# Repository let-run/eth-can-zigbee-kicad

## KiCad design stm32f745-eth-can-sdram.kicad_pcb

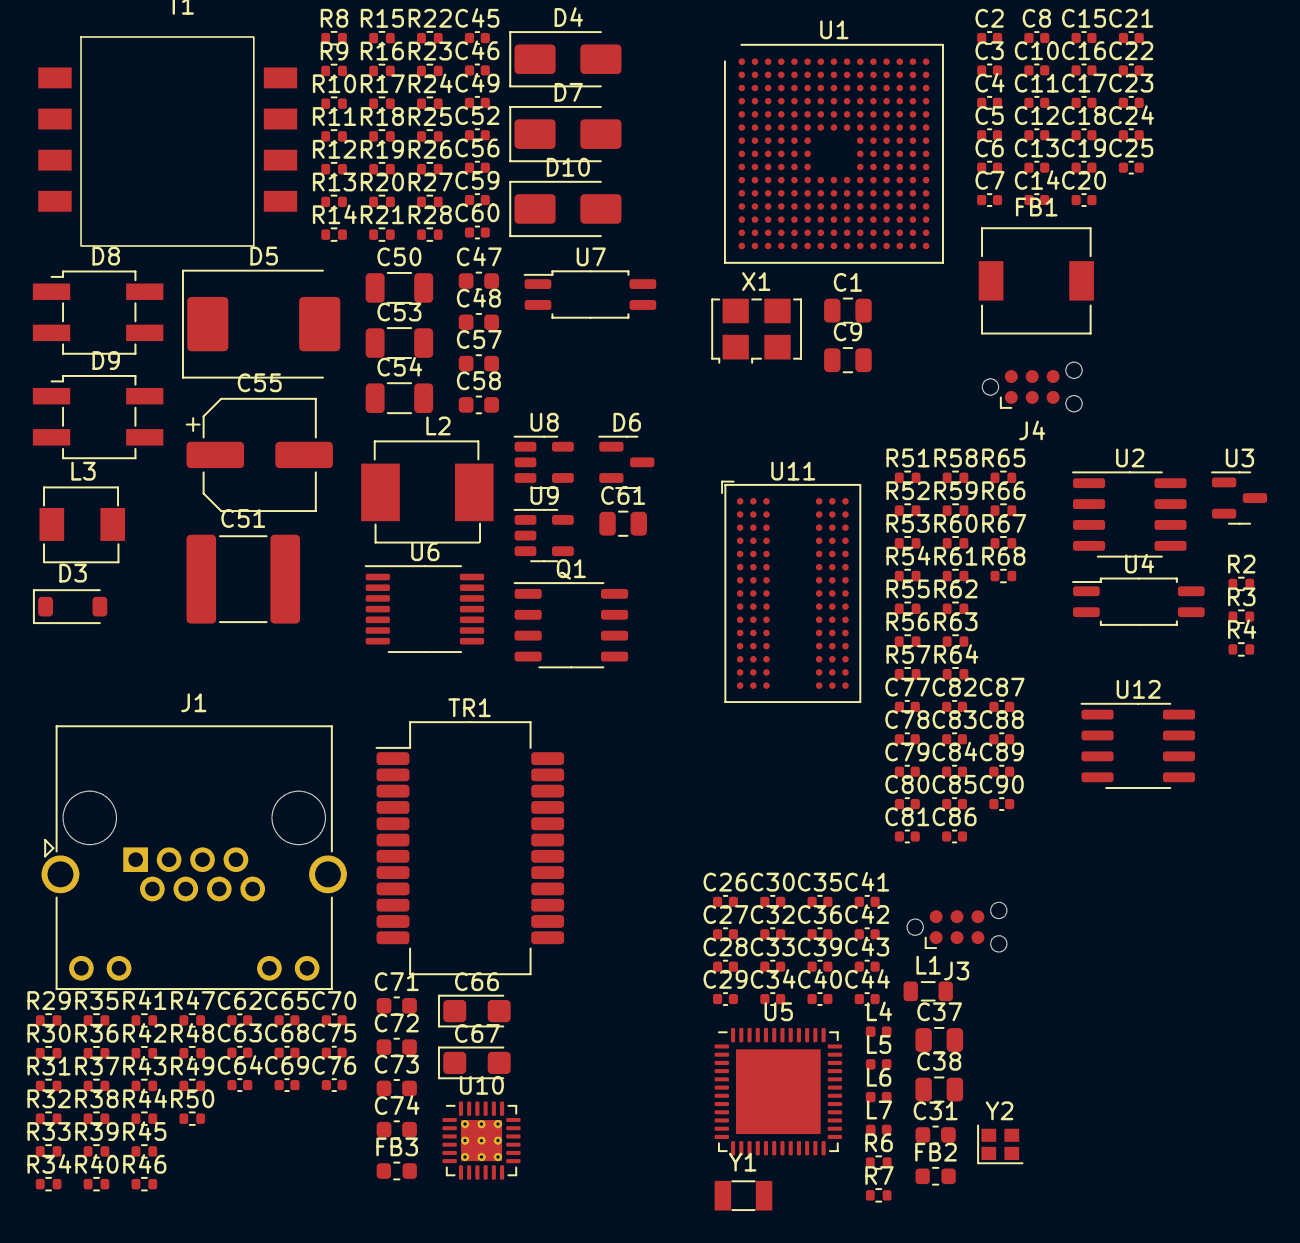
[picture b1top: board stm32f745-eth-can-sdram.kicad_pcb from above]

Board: 2 copper layers, 195 parts (0 on the bottom side), 148 nets, no tracks yet.

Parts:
C1: 100n; C_0805_2012Metric
C2: 10u; C_0402_1005Metric
C3, C5, C7, C8, C10, C11, C12, C13, C14, C15, C16, C17, C18, C19, C20, C21, C22, C23, C24, C25, C32, C33, C34, C35, C36, C39, C40, C46, C62, C63, C64, C65, C68, C76, C77, C78, C79, C80, C81, C82, C83, C84, C85, C86, C87, C88, C89, C90: 100n; C_0402_1005Metric
C4: 10n; C_0402_1005Metric
C6: 1u; C_0402_1005Metric
C9: 1u; C_0805_2012Metric
C26, C27, C28, C41, C42, C43, C44: 1pF; C_0402_1005Metric
C29, C30: 12pF; C_0402_1005Metric
C31, C48: 10uF; C_0603_1608Metric
C37, C38: 22uF; C_0805_2012Metric
C45, C75: DNP; C_0402_1005Metric
C47: 1uF; C_0603_1608Metric
C49, C60: 0.1uF; C_0402_1005Metric
C50: 2.2uF; C_1206_3216Metric
C51: 10uF; C_2220_5650Metric
C52: 1000pF; C_0402_1005Metric
C53, C54: 22uF; C_1206_3216Metric
C55: 470uF; CP_Elec_6.3x7.7
C56, C69: 1uF; C_0402_1005Metric
C57: 0.015uF; C_0603_1608Metric
C58: 470pF; C_0603_1608Metric
C59: 0.022uF; C_0402_1005Metric
C61: 1000pF; C_0805_2012Metric
C66, C67: 10uF; CP_EIA-3216-18_Kemet-A
C70: 470pF; C_0402_1005Metric
C71, C72, C73, C74: 22nF; C_0603_1608Metric
D3: MMSD4148; D_SOD-123
D4, D10: MURA120; D_SMA
D5: MBRS540; D_SMC
D6: BAT54S; SOT-23
D7: SMAJ58A; D_SMA
D8, D9: HD01
FB1: 120R; L_6.3x6.3_H3
FB2: BLM18HE152SN1D; L_0603_1608Metric
FB3: BLM18PG121; L_0603_1608Metric
J1: 8P8C_LED_Shielded; RJ45_Amphenol_RJHSE538X
J3: JTAG; Tag-Connect_TC2030-IDC-NL_2x03_P1.27mm_Vertical
J4: SWO; Tag-Connect_TC2030-IDC-NL_2x03_P1.27mm_Vertical
L1: 6.8uH; L_0805_2012Metric
L2: 3.3uH; L_6.6x7.2_H3
L3: 0.33uH; L_4.4x4.2_H2
L4: LQG15HS1(2nH); L_0402_1005Metric
L5: LQG15HS2(2nH); L_0402_1005Metric
L6, L7: LQG15HS2(2.4nH); L_0402_1005Metric
Q1: Si4848DY; SOP-8_3.9x4.9mm_P1.27mm
R2: 40k; R_0402_1005Metric
R3: 5k; R_0402_1005Metric
R4: 575; R_0402_1005Metric
R6, R7: 1k; R_0402_1005Metric
R8: 24.9k; R_0402_1005Metric
R9: 1.27k; R_0402_1005Metric
R10: 39.2k; R_0402_1005Metric
R11: 80.6k; R_0402_1005Metric
R12: 59k; R_0402_1005Metric
R13: 392k; R_0402_1005Metric
R14, R17, R18, R20: 10R; R_0402_1005Metric
R15, R22: 1K; R_0402_1005Metric
R16: 0.5(0.25W); R_0402_1005Metric
R19: 39K; R_0402_1005Metric
R21: 575R; R_0402_1005Metric
R23: 2K; R_0402_1005Metric
R24: 11K; R_0402_1005Metric
R25: 34K; R_0402_1005Metric
R26: 1.5K; R_0402_1005Metric
R27: 301R; R_0402_1005Metric
R28: 0; R_0402_1005Metric
R29, R30, R31: 33; R_0402_1005Metric
R32: 100; R_0402_1005Metric
R33, R34, R35, R36, R37: 4.7K; R_0402_1005Metric
R38, R39, R40, R41: 50; R_0402_1005Metric
R42: 12.1K; R_0402_1005Metric
R43, R44: 330; R_0402_1005Metric
R45, R46, R51, R52, R53, R54, R55, R56, R57, R58, R59, R60, R61, R62, R63, R64, R65, R66, R67, R68: 10K; R_0402_1005Metric
R47, R48, R49, R50: 75; R_0402_1005Metric
T1: POE70P-50L; POE70P
TR1: 30F-51NL; Transformer_Ethernet_YDS_30F-51NL_SO-24_7.1x15.1mm
U1: STM32F746NGHx; TFBGA-216_13x13mm_Layout15x15_P0.8mm
U2, U12: TJA1051T; SOIC-8_3.9x4.9mm_P1.27mm
U3: TL431(2.5-36); SOT-23
U4, U7: TCMT1107; SOP-4_4.4x2.6mm_P1.27mm
U5: VQFN-48-1EP_7x7mm_P0.5mm_EP5.15x5.15mm
U6: TPS23753; TSSOP-14_4.4x5mm_P0.65mm
U8: TLV431AIDBVR; SOT-23-5
U9: TPS73633DBV; SOT-23-5
U10: LAN8742A; VQFN-24-1EP_4x4mm_P0.5mm_EP2.5x2.5mm_ThermalVias
U11: IS42S32800J-7BLI; BGA-90_8.0x13.0mm_Layout2x3x15_P0.8mm
X1: SG-5032CAN; Oscillator_SMD_SeikoEpson_SG8002LB-4Pin_5.0x3.2mm
Y1: 32.768kHz; Crystal_SMD_3215-2Pin_3.2x1.5mm
Y2: Q22FA12800150; Crystal_SMD_2016-4Pin_2.0x1.6mm

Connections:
+3.3V: C2.1, C3.1, C5.1, C7.1, C8.1, C9.1, C10.1, C11.1, C12.1, C13.1, C14.1, C15.1, C16.1, C17.1, C18.1, C19.1, C20.1, C21.1, C22.1, C23.1, C24.1, C25.1, C62.1, C63.1, C67.1, C68.1, C76.1, C77.1, C78.1, C79.1, C80.1, C81.1, C82.1, C83.1, C84.1, C85.1, C86.1, C87.1, C88.1, C89.1, C90.1, FB1.1, FB2.2, FB3.2, J4.5 (GND), R33.2, R34.2, R35.2, R36.2, R37.2, R38.2, R39.2, R40.2, R41.2, TR1.7 (CT), TR1.10 (CT), U1.C1 (VBAT), U1.E7 (VDD), U1.E8 (VDD), U1.E9 (VDD), U1.E10 (VDD), U1.F4 (VDD), U1.F5 (VDD), U1.F11 (VDD), U1.G5 (VDD), U1.H5 (VDD), U1.H11 (VDD), U1.J5 (VDD), U1.J11 (VDD), U1.K5 (VDD), U1.K11 (VDD), U1.L7 (VDD), U1.L8 (VDD), U1.L9 (VDD), U1.L10 (VDD), U10.9 (VDDIO), U11.A7 (VDD), U11.B2 (VDDQ), U11.B7 (VDDQ), U11.C9 (VDDQ), U11.D9 (VDDQ), U11.E1 (VDDQ), U11.F9 (VDD), U11.L1 (VDDQ), U11.L7 (VDD), U11.M9 (VDDQ), U11.N9 (VDDQ), U11.P2 (VDDQ), U11.P7 (VDDQ), U11.R7 (VDD)
+3.3VA: C4.1, C6.1, FB1.2
+5V: C55.1, L3.2, R28.2, U2.3 (VCC), U12.3 (VCC)
+24V: R2.2, R4.2
/Zigbee/DCDC_SW: L1.1, U5.33 (DCDC_SW)
/Zigbee/VDDR: C38.1, C39.1, C40.1, L1.2, U5.45 (VDDR), U5.48 (VDDR_RF)
/Zigbee/VDDS: C33.1, C34.1, C35.1, C36.1, C37.1, FB2.1, U5.13 (VDDS2), U5.22 (VDDS3), U5.34 (VDDS_DCDC), U5.44 (VDDS)
AUX: D10.2 (A), R13.2
ETH_LED1: J1.12, R46.2, U10.3 (LED1/REGOFF)
ETH_LED2: J1.10, R45.1, U10.2 (LED2/~INTSEL)
FMC_A0: U1.D2 (PF0), U11.G8 (A0)
FMC_A1: U1.E2 (PF1), U11.G9 (A1)
FMC_A2: U1.G2 (PF2), U11.F7 (A2)
FMC_A3: U1.H2 (PF3), U11.F3 (A3)
FMC_A4: U1.J2 (PF4), U11.G1 (A4)
FMC_A5: U1.K3 (PF5), U11.G2 (A5)
FMC_A6: U1.M6 (PF12), U11.G3 (A6)
FMC_A7: U1.N6 (PF13), U11.H1 (A7)
FMC_A8: U1.M8 (PF15), U1.P6 (PF14), U11.H2 (A8)
FMC_A10: U1.N7 (PG0), U11.G7 (A10)
FMC_A11: U1.M7 (PG1), U11.H9 (A11)
FMC_BA0: U1.N12 (PG4), U11.J7 (BA0)
FMC_BA1: U1.N11 (PG5), U11.H8 (BA1)
FMC_D0: U1.L12 (PD14), U11.R8 (DQ0)
FMC_D1: U1.K13 (PD15), U11.N7 (DQ1)
FMC_D2: U1.B12 (PD0), U11.R9 (DQ2)
FMC_D3: U1.C12 (PD1), U11.N8 (DQ3)
FMC_D4: U1.R8 (PE7), U11.P9 (DQ4)
FMC_D5: U1.N9 (PE8), U11.M8 (DQ5)
FMC_D6: U1.P9 (PE9), U11.M7 (DQ6)
FMC_D7: U1.R9 (PE10), U11.L8 (DQ7)
FMC_D8: U1.P10 (PE11), U11.L2 (DQ8)
FMC_D9: U1.R10 (PE12), U11.M3 (DQ9)
FMC_D10: U1.R12 (PE13), U11.M2 (DQ10)
FMC_D11: U1.P11 (PE14), U11.P1 (DQ11)
FMC_D12: U1.R11 (PE15), U11.N2 (DQ12)
FMC_D13: U1.L15 (PD8), U11.R1 (DQ13)
FMC_D14: U1.L14 (PD9), U11.N3 (DQ14)
FMC_D15: U1.K15 (PD10), U11.R2 (DQ15)
FMC_NBL0: U1.A6 (PE0), U11.K9 (DQM0)
FMC_NBL1: U1.A5 (PE1), U11.K1 (DQM1)
FMC_SDCKE0: U1.K4 (PH2), U11.J2 (CKE)
FMC_SDCLK: U1.H14 (PG8), U11.J1 (CLK)
FMC_SDNCAS: U1.B7 (PG15), U11.K7 (~CAS)
FMC_SDNE0: U1.J4 (PH3), U11.J8 (~CS)
FMC_SDNRAS: U1.P8 (PF11), U11.J9 (~RAS)
FMC_SDNWE: U1.J3 (PH5), U11.K8 (~WE)
GND: C1.2, C2.2, C3.2, C4.2, C5.2, C6.2, C7.2, C8.2, C9.2, C10.2, C11.2, C12.2, C13.2, C14.2, C15.2, C16.2, C17.2, C18.2, C19.2, C20.2, C21.2, C22.2, C23.2, C24.2, C25.2, C26.2, C27.2, C29.1, C31.2, C32.2, C33.2, C34.2, C35.2, C36.2, C37.2, C38.2, C39.2, C40.2, C41.2, C42.2, C43.2, C44.2, C53.2, C54.2, C55.2, C56.2, C62.2, C63.2, C64.2, C65.2, C66.2, C67.2, C68.2, C69.1, C70.1, C75.2, C76.2, C77.2, C78.2, C79.2, C80.2, C81.2, C82.2, C83.2, C84.2, C85.2, C86.2, C87.2, C88.2, C89.2, C90.2, J3.5 (GND), J4.1 (VCC), R6.2, R7.2, R24.1, R42.1, R43.2, R44.1, R45.2, R46.1, R51.2, R52.2, R53.2, R54.2, R55.2, R56.2, R57.2, R58.2, R59.2, R60.2, R61.2, R62.2, R63.2, R64.2, R65.2, R66.2, R67.2, R68.2, T1.5, T1.6, U2.2 (GND), U2.8 (S), U5.49 (EP), U8.5 (A), U10.25 (VSS), U11.A3 (VSS), U11.B3 (VSSQ), U11.B8 (VSSQ), U11.C1 (VSSQ), U11.D1 (VSSQ), U11.E9 (VSSQ), U11.F1 (VSS), U11.L3 (VSS), U11.L9 (VSSQ), U11.M1 (VSSQ), U11.N1 (VSSQ), U11.P3 (VSSQ), U11.P8 (VSSQ), U11.R3 (VSS), U12.2 (GND), U12.8 (S), Y2.2, Y2.4
GND1: C45.2, C46.2, C47.2, C48.2, C50.2, C51.2, J1.SH, R3.1, R10.1, R11.1, R12.1, R16.1, T1.2, U3.3 (A), U6.6 (RTN), U7.3
JTAG_TCK: J3.4 (SWCLK), U5.25 (JTAG_TCKC)
JTAG_TDI: J3.2 (SWDIO), U5.27 (DIO_17)
JTAG_TDO: J3.6 (SWO), U5.26 (DIO_16)
JTAG_TMS: J3.1 (VCC), U5.24 (JTAG_TMSC)
NRST: C1.1, J4.3 (~RESET), U1.J1 (NRST), U10.15 (~RST)
unnamed: C26.1, L4.1, L5.2
unnamed: C28.1, L5.1, L6.2
unnamed: C29.2, L7.2
unnamed: C30.2, L4.2
unnamed: C49.1, C50.1, L2.2, R19.2, T1.3
unnamed: C52.1, R20.2
unnamed: C57.1, R23.1
unnamed: C59.1, R27.2
unnamed: C71.1, R49.1
unnamed: C72.1, R47.1
unnamed: C73.1, R50.1
unnamed: C74.1, R48.1
unnamed: C75.1, R47.2, R48.2, R49.2, R50.2
unnamed: D3.2 (A), R17.1
unnamed: C47.1, C48.1, D3.1 (K)
unnamed: D4.2 (A), Q1.5 (D), Q1.6 (D), Q1.7 (D), Q1.8 (D), T1.4
unnamed: C49.2, D4.1 (K), R19.1
unnamed: D5.2 (A), R20.1, T1.7, T1.8
unnamed: C52.2, C53.1, C54.1, D5.1 (K), L3.1
unnamed: C58.1, D6.1 (A), R23.2, U7.2, U8.3 (K)
unnamed: C56.1, D6.3 (COM), R22.1
unnamed: D6.2 (K), R21.2, R22.2, R25.2, R28.1
unnamed: J1.9, R43.1
unnamed: J1.11, R44.2
unnamed: Q1.4 (G), R14.2
unnamed: Q1.1 (S), Q1.2 (S), Q1.3 (S), R15.2, R16.2
unnamed: R4.1, U4.1
unnamed: R17.2, R18.1
unnamed: R18.2, T1.1
unnamed: R21.1, U7.1
unnamed: J1.6, TR1.17 (MX3+)
unnamed: J1.3, TR1.16 (MX3-)
unnamed: J1.2, TR1.14 (MX4+)
unnamed: J1.1, TR1.13 (MX4-)
unnamed: U1.F2 (VSS), U1.F6 (VSS), U1.F7 (VSS), U1.F8 (VSS), U1.F9 (VSS), U1.F10 (VSS), U1.G6 (VSS), U1.G10 (VSS), U1.H6 (VSS), U1.H10 (VSS), U1.J6 (VSS), U1.J10 (VSS), U1.K6 (VSS), U1.K7 (VSS), U1.K8 (VSS), U1.K9 (VSS), U1.K10 (VSS), U1.L6 (VSS)
unnamed: U3.1 (K), U4.2
unnamed: R2.1, R3.2, U3.2 (REF)
unnamed: C31.1, U5.23 (DCOUPL)
unnamed: C27.1, L6.1, U5.2 (RF_N)
unnamed: C28.2, L7.1, U5.1 (RF_P)
unnamed: R10.2, R13.1, U6.12 (APD)
unnamed: R11.2, U6.13 (BLNK)
unnamed: R9.2, U6.11 (CLS)
unnamed: C45.1, R15.1, U6.3 (CS)
unnamed: R26.1, R27.1, U6.1 (CTL), U7.4
unnamed: R8.1, U6.10 (DEN)
unnamed: R12.2, U6.14 (FRS)
unnamed: R14.1, U6.5 (GATE)
unnamed: C57.2, C58.2, R24.2, R25.1, U8.4 (REF)
unnamed: R31.2, R33.1, U10.11 (CRS_DV/MODE2)
unnamed: R42.2, U10.24 (RBIAS)
unnamed: R29.2, R35.1, U10.8 (RXD0/MODE0)
unnamed: R30.2, R34.1, U10.7 (RXD1/MODE1)
unnamed: C64.1, C65.1, C66.1, FB3.1, U10.1 (VDD2A), U10.19 (VDD1A)
unnamed: C69.2, C70.2, U10.6 (VDDCR)
unnamed: R32.2, U10.5 (XTAL1/CLKIN)
unnamed: R51.1, U11.E8 (DQ16)
unnamed: R52.1, U11.D7 (DQ17)
unnamed: R53.1, U11.D8 (DQ18)
unnamed: R54.1, U11.B9 (DQ19)
unnamed: R55.1, U11.C8 (DQ20)
unnamed: R56.1, U11.A9 (DQ21)
unnamed: R57.1, U11.C7 (DQ22)
unnamed: R58.1, U11.A8 (DQ23)
unnamed: R59.1, U11.A2 (DQ24)
unnamed: R60.1, U11.C3 (DQ25)
unnamed: R61.1, U11.A1 (DQ26)
unnamed: R62.1, U11.C2 (DQ27)
unnamed: R63.1, U11.B1 (DQ28)
unnamed: R64.1, U11.D2 (DQ29)
unnamed: R65.1, U11.D3 (DQ30)
unnamed: R66.1, U11.E2 (DQ31)
unnamed: R67.1, U11.F8 (DQM2)
unnamed: R68.1, U11.F2 (DQM3)
POE_VDD: C51.1, C60.1, C61.1, D7.1 (A1), D8.1 (+), D9.1 (+), D10.1 (K), L2.1, R8.2, U6.8 (VDD1), U6.9 (VDD)
POE_VSS: C60.2, C61.2, D7.2 (A2), D8.2 (-), D9.2 (-), R9.1, U6.7 (VSS)
RMII_MDIO: R37.1, U10.12 (MDIO)
RMII_REF_CLK: R36.1, U10.14 (~INT/REFCLKO)
RX+: R40.1, TR1.9 (TD3-), U10.23 (RXP)
RX-: R41.1, TR1.8 (TD3+), U10.22 (RXN)
SWCLK: J4.4 (SWCLK), U1.A14
SWDIO: J4.2 (SWDIO), U1.A15 (PA13)
TX+: R38.1, TR1.12 (TD4-), U10.21 (TXP)
TX-: R39.1, TR1.11 (TD4+), U10.20 (TXN)
VB: C46.1, C59.2, R26.2, U6.2 (VB)
VC1N: C71.2, D8.4, TR1.18 (CT)
VC1P: C74.2, D8.3, TR1.15 (CT)
VC2N: C73.2, D9.4, J1.4, J1.5
VC2P: C72.2, D9.3, J1.7, J1.8
X32Q1: C41.1, U5.3 (X32K_Q1), Y1.1
X32Q2: C42.1, U5.4 (X32K_Q2), Y1.2
X48M_N: C43.1, U5.46 (X48M_N), Y2.3
X48M_P: C44.1, U5.47 (X48M_P), Y2.1
nRESET: C32.1, J3.3 (~RESET), U5.35 (RESET_N)

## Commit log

2023-09-10 inital scheme
2023-09-11 add POE schematics, Ethernet phy
2023-09-18 almost final schematics
